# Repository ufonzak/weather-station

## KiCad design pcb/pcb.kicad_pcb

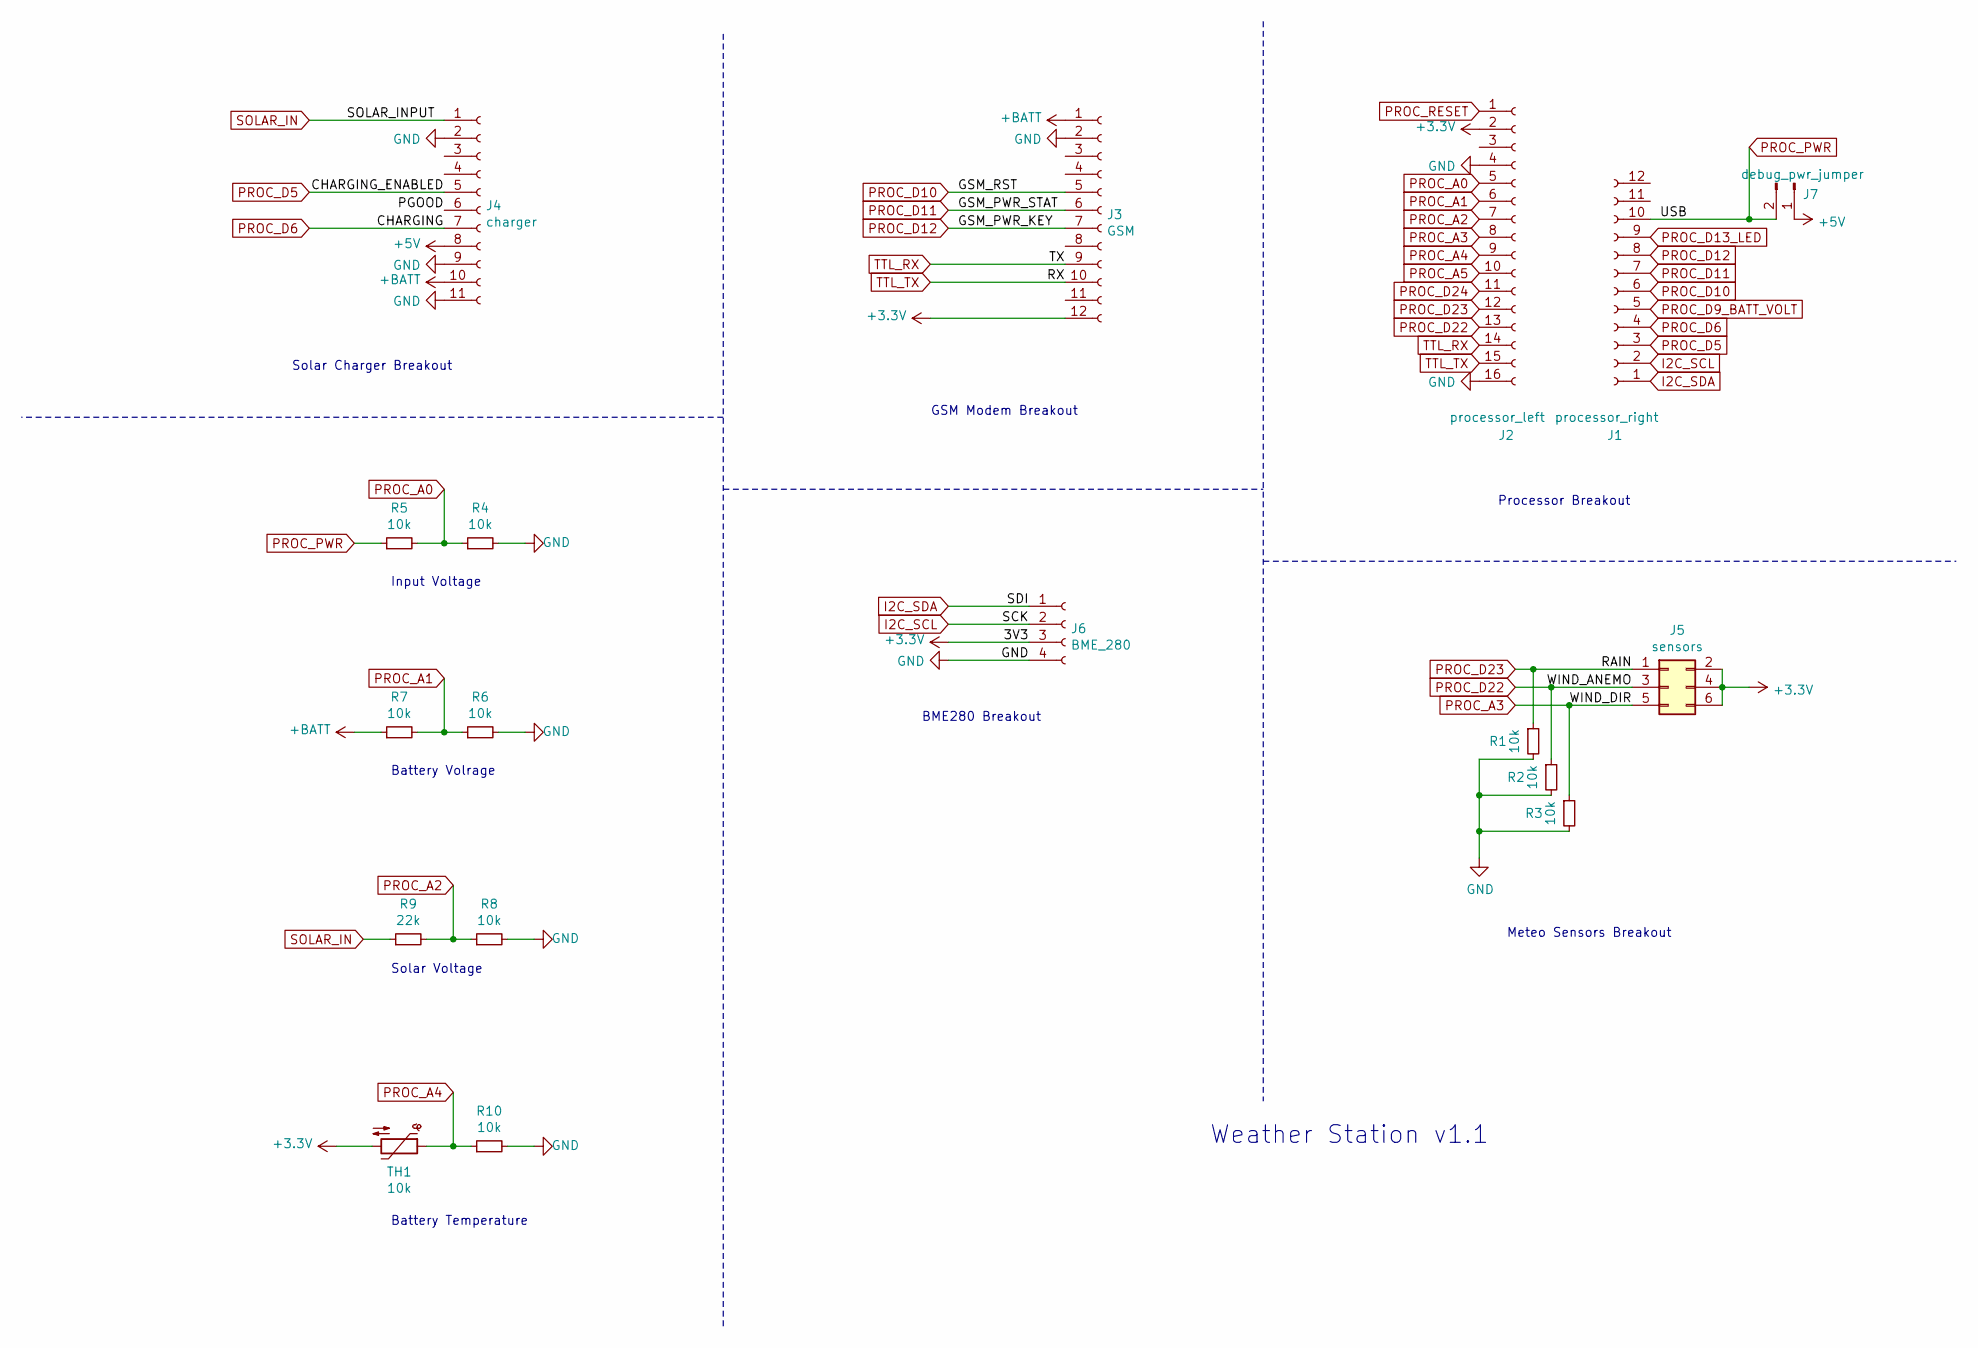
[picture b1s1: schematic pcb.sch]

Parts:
J1: processor_right; PinSocket_1x12_P2.54mm_Vertical
J2: processor_left; PinSocket_1x16_P2.54mm_Vertical
J3: GSM; PinSocket_1x12_P2.54mm_Vertical
J4: charger; PinSocket_1x11_P2.54mm_Vertical
J5: sensors; PinSocket_2x03_P2.54mm_Vertical
J6: BME_280; JST_PH_B4B-PH-K_1x04_P2.00mm_Vertical
J7: debug_pwr_jumper; PinHeader_1x02_P2.54mm_Vertical
R1, R2, R3, R4, R5, R6, R7, R8, R10: 10k; R_Axial_DIN0207_L6.3mm_D2.5mm_P10.16mm_Horizontal
R9: 22k; R_Axial_DIN0207_L6.3mm_D2.5mm_P10.16mm_Horizontal
TH1: 10k; R_Axial_DIN0204_L3.6mm_D1.6mm_P5.08mm_Horizontal

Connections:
+3V3: J2.2, J3.12, J5.2, J5.4, J5.6, J6.3, TH1.2
+5V: J4.8, J7.1
+BATT: J3.1, J4.10, R7.1
/PGOOD: J4.6
GND: J2.4, J2.16, J3.2, J4.2, J4.9, J4.11, J6.4, R1.2, R2.2, R3.2, R4.2, R6.2, R8.2, R10.2
I2C_SCL: J1.2, J6.2
I2C_SDA: J1.1, J6.1
PROC_A0: J2.5, R4.1, R5.2
PROC_A1: J2.6, R6.1, R7.2
PROC_A2: J2.7, R8.1, R9.2
PROC_A3: J2.8, J5.5, R3.1
PROC_A4: J2.9, R10.1, TH1.1
PROC_A5: J2.10
PROC_D5: J1.3, J4.5
PROC_D6: J1.4, J4.7
PROC_D9_BATT_VOLT: J1.5
PROC_D10: J1.6, J3.5
PROC_D11: J1.7, J3.6
PROC_D12: J1.8, J3.7
PROC_D13_LED: J1.9
PROC_D22: J2.13, J5.3, R2.1
PROC_D23: J2.12, J5.1, R1.1
PROC_D24: J2.11
PROC_PWR: J1.10, J7.2, R5.1
PROC_RESET: J2.1
SOLAR_IN: J4.1, R9.1
TTL_RX: J2.14, J3.9
TTL_TX: J2.15, J3.10

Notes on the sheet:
Processor Breakout
Meteo Sensors Breakout
BME280 Breakout
Input Voltage
Battery Volrage
Solar Voltage
Battery Temperature
GSM Modem Breakout
Solar Charger Breakout
Weather Station v1.1

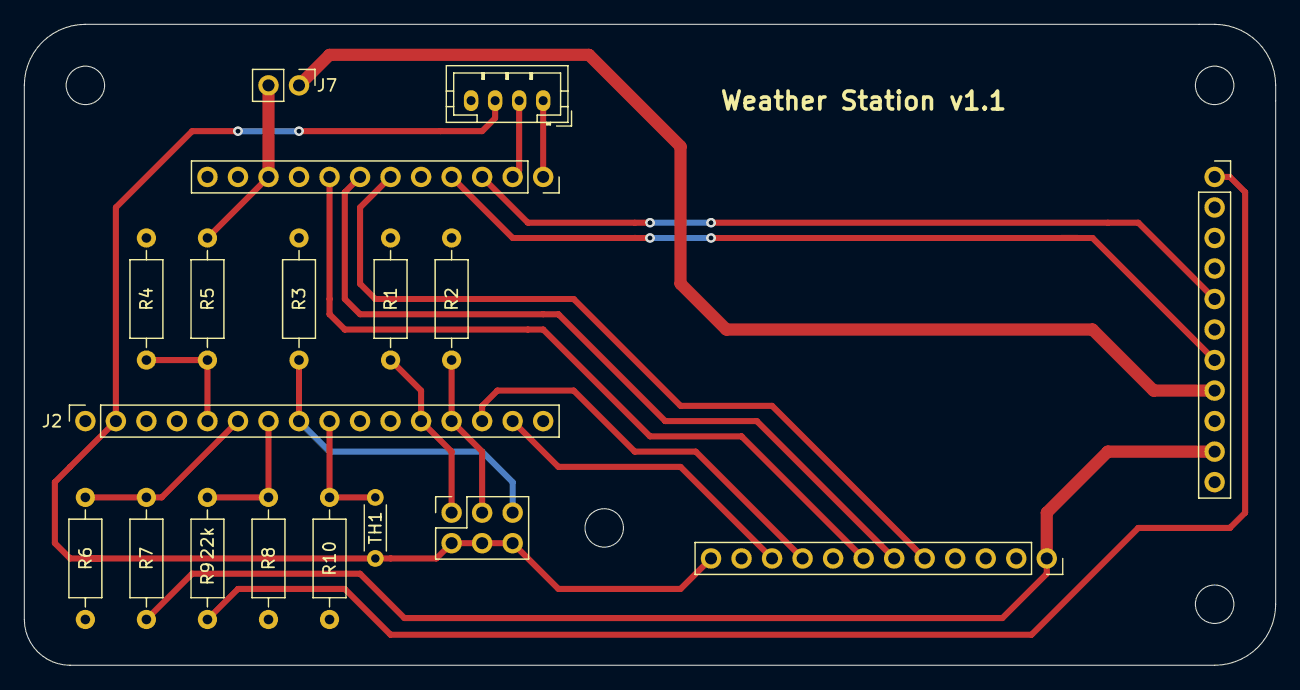
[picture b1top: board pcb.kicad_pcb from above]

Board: 2 copper layers, 104.1 x 53.3 mm, 18 parts (0 on the bottom side), 22 nets.

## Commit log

2020-10-27 Voltage measuring.
2020-10-27 Cleanup and averaging.
2020-11-02 Power supply regulations
2020-11-08 REgulated supply only.
2020-11-08 breakdown to files
2020-11-09 Basic weather sensing
2020-11-09 Uptime and rain
2020-11-12 Adding BME data.
2020-11-15 Measuring battery tep
2020-12-23 Gust sampling and send boost.
2021-01-04 Automate reseting of i2c
2021-02-15 Getting all the data.
2021-02-24 Styling everything.
2021-02-24 Doubling line thickness
2021-02-26 Fixes.
2021-03-01 New pins, data format and battery charging control.
2021-03-11 More upgrades.
2021-03-13 New PCB.
2021-03-17 No dynamic allocation.
2021-03-20 Watchdog.
2021-03-20 Resetting on sending failure.
2021-03-21 Cloud data.
2021-03-21 Gsm data.
2021-03-23 Refactoring.
2021-03-23 Fixing the wind.
2021-03-27 Fixing cycleLength overflow.
2021-03-28 Adjusting timeouts, cycle.
2021-04-01 Fixing web.
2021-04-01 Fixing charts.
2021-04-10 Separating temperature and cycle control.
2021-08-23 Adding multi-site support.
2021-09-04 Removing BME data from other sites.
2023-03-26 Better charts.
2023-03-26 Fixes and camera integration.
2023-04-10 Removing BME.
2023-07-21 Shopping list.
